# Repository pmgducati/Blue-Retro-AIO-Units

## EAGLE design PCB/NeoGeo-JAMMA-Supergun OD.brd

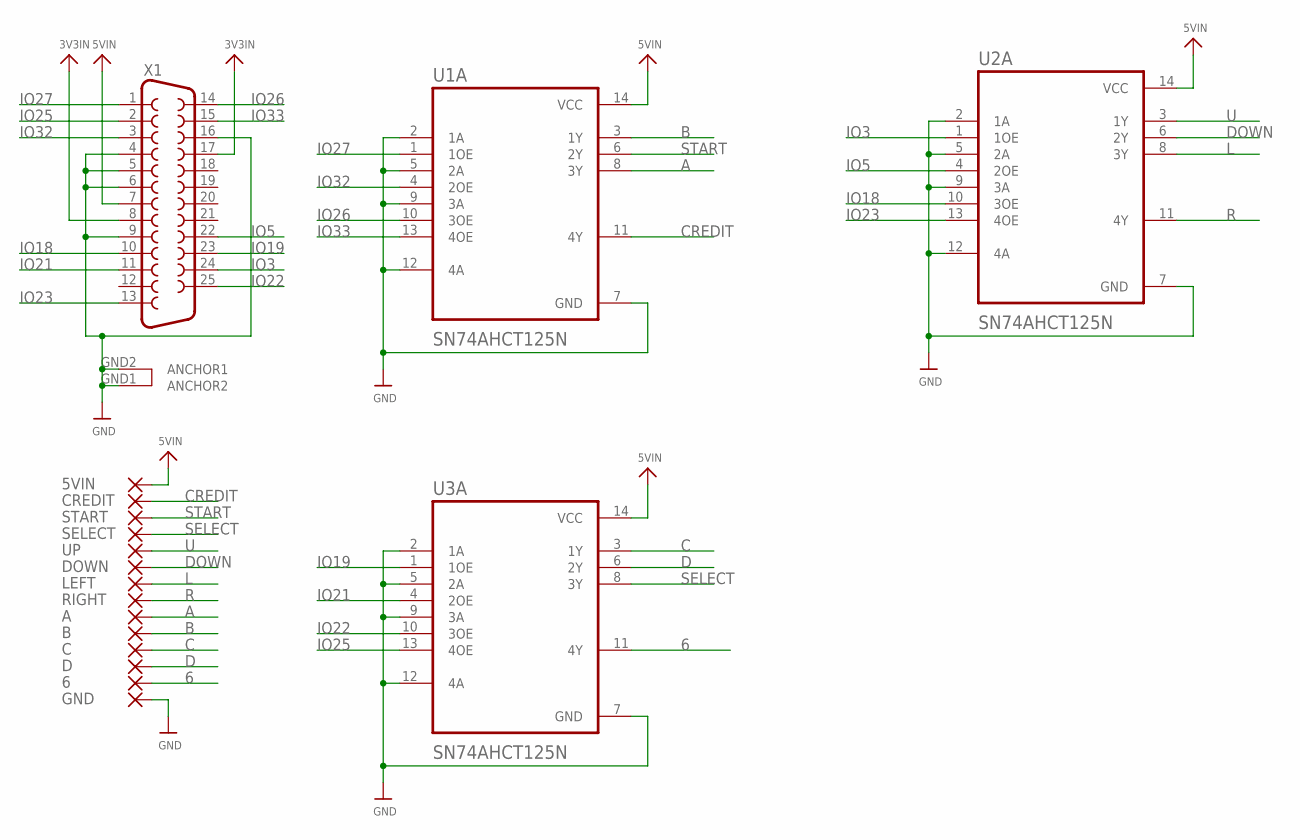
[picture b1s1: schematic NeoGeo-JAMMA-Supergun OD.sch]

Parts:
5VIN, 6: SMD5; SMD2,54-5,08
A: SMD5; SMD2,54-5,08
B: SMD5; SMD2,54-5,08
C: SMD5; SMD2,54-5,08
CREDIT: SMD5; SMD2,54-5,08
D: SMD5; SMD2,54-5,08
DOWN: SMD5; SMD2,54-5,08
GND: SMD5; SMD2,54-5,08
LEFT: SMD5; SMD2,54-5,08
RIGHT: SMD5; SMD2,54-5,08
SELECT: SMD5; SMD2,54-5,08
START: SMD5; SMD2,54-5,08
U1A, U2A, U3A: SN74AHCT125N; DIP794W45P254L1969H508Q14
UP: SMD5; SMD2,54-5,08
X1: DB25_FEMALEHP; F25HP

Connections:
3V3IN: X1.8, X1.17
5VIN: 5VIN.1, U1A.14 (VCC), U2A.14 (VCC), U3A.14 (VCC), X1.7
6: 6.1, U3A.11 (4Y)
A: A.1, U1A.8 (3Y)
B: B.1, U1A.3 (1Y)
C: C.1, U3A.3 (1Y)
CREDIT: CREDIT.1, U1A.11 (4Y)
D: D.1, U3A.6 (2Y)
DOWN: DOWN.1, U2A.6 (2Y)
GND: GND.1, U1A.2 (1A), U1A.5 (2A), U1A.7 (GND), U1A.9 (3A), U1A.12 (4A), U2A.2 (1A), U2A.5 (2A), U2A.7 (GND), U2A.9 (3A), U2A.12 (4A), U3A.2 (1A), U3A.5 (2A), U3A.7 (GND), U3A.9 (3A), U3A.12 (4A), X1.4, X1.5, X1.6, X1.9, X1.16, X1.GND1 (ANCHOR2), X1.GND2 (ANCHOR1)
IO3: U2A.1 (1OE), X1.24
IO5: U2A.4 (2OE), X1.22
IO18: U2A.10 (3OE), X1.10
IO19: U3A.1 (1OE), X1.23
IO21: U3A.4 (2OE), X1.11
IO22: U3A.10 (3OE), X1.25
IO23: U2A.13 (4OE), X1.13
IO25: U3A.13 (4OE), X1.2
IO26: U1A.10 (3OE), X1.14
IO27: U1A.1 (1OE), X1.1
IO32: U1A.4 (2OE), X1.3
IO33: U1A.13 (4OE), X1.15
L: LEFT.1, U2A.8 (3Y)
R: RIGHT.1, U2A.11 (4Y)
SELECT: SELECT.1, U3A.8 (3Y)
START: START.1, U1A.6 (2Y)
U: U2A.3 (1Y), UP.1

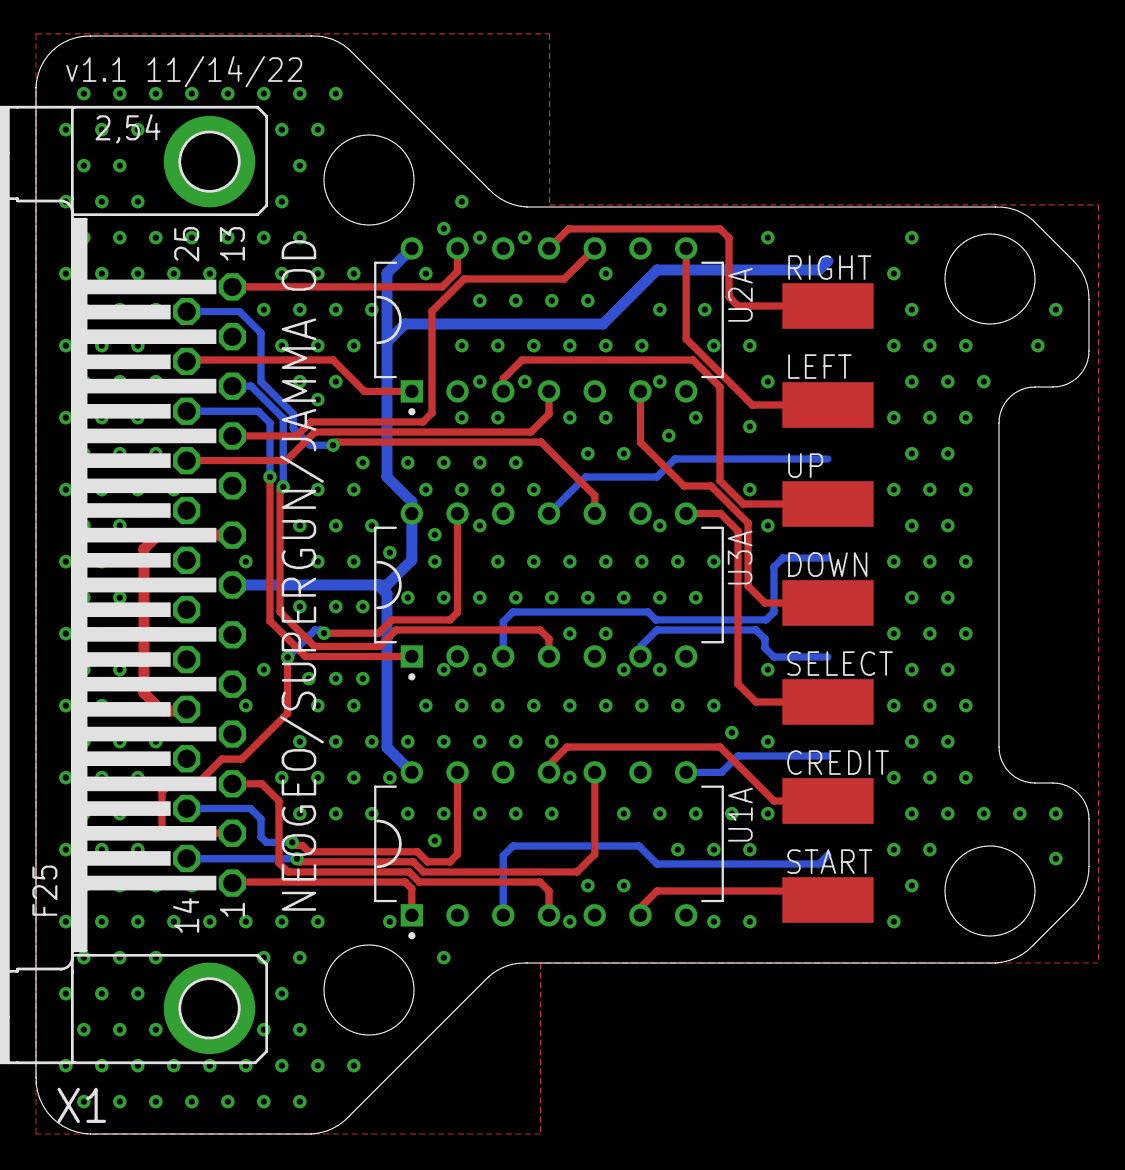
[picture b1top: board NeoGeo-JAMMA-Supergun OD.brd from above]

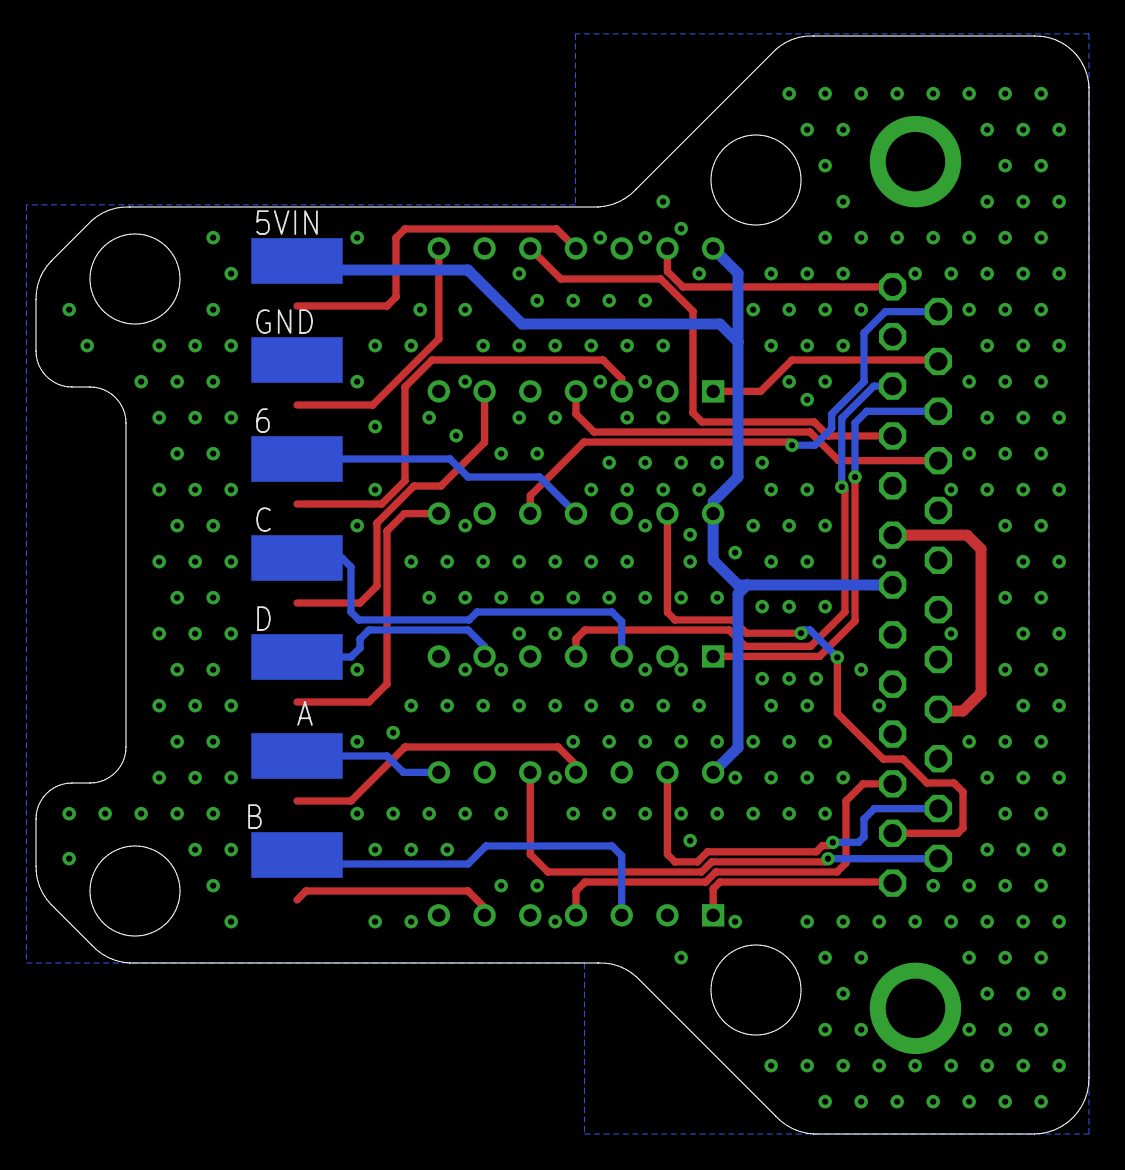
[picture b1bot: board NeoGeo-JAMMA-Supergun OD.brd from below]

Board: 2 copper layers, 58.5 x 61.0 mm, 18 parts (7 on the bottom side), 27 nets.

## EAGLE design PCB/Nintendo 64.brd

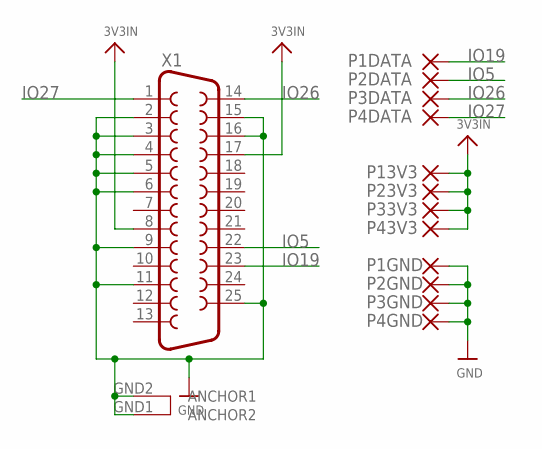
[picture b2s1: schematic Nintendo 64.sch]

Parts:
P1DATA, P1GND, P2DATA, P2GND, P3DATA, P3GND, P4DATA, P4GND, P13V3, P23V3, P33V3, P43V3: SMD5; SMD2,54-5,08
X1: DB25_FEMALEHP; F25HP

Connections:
3V3IN: P13V3.1, P23V3.1, P33V3.1, P43V3.1, X1.8, X1.17
GND: P1GND.1, P2GND.1, P3GND.1, P4GND.1, X1.2, X1.3, X1.4, X1.5, X1.6, X1.9, X1.11, X1.15, X1.16, X1.25, X1.GND1 (ANCHOR2), X1.GND2 (ANCHOR1)
IO5: P2DATA.1, X1.22
IO19: P1DATA.1, X1.23
IO26: P3DATA.1, X1.14
IO27: P4DATA.1, X1.1

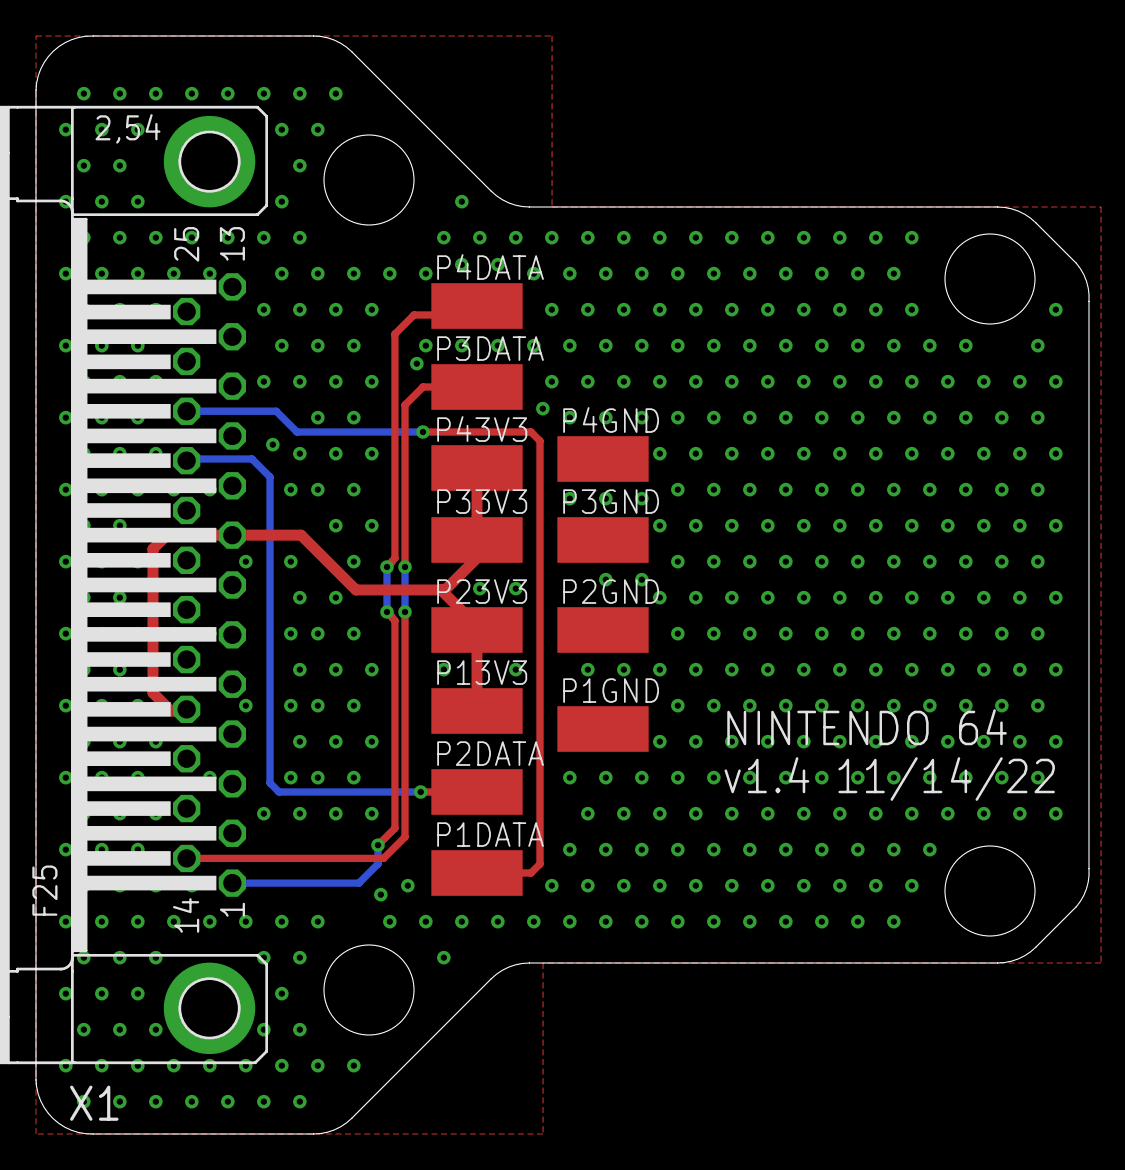
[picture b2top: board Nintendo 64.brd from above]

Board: 2 copper layers, 58.5 x 61.0 mm, 13 parts (0 on the bottom side), 6 nets.

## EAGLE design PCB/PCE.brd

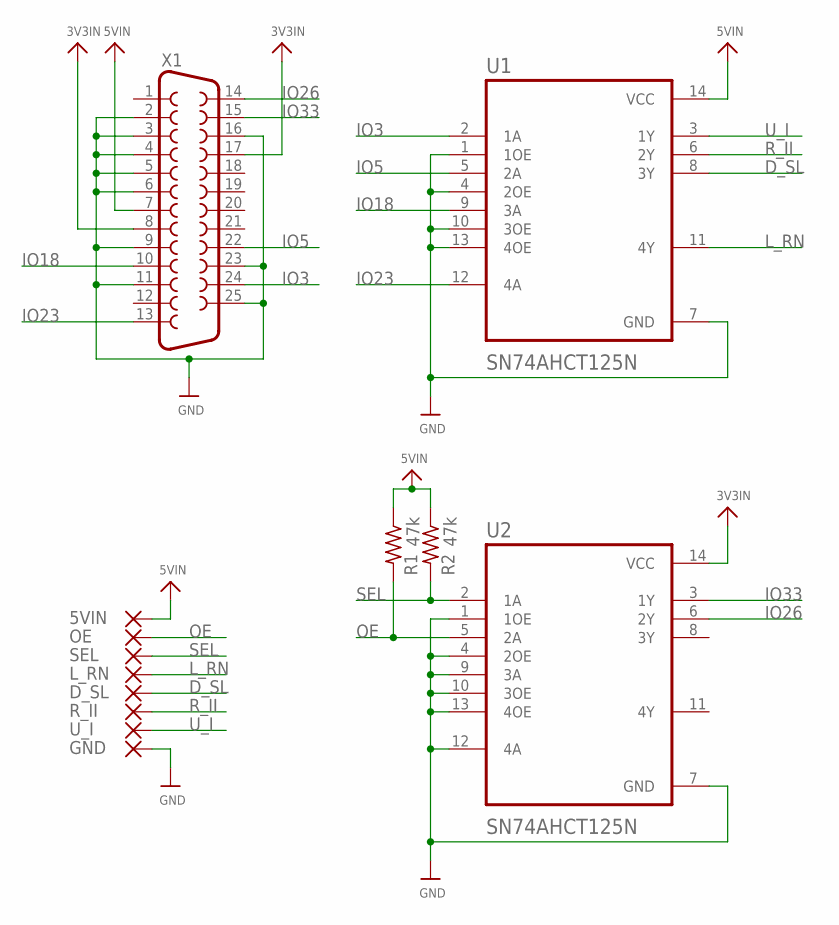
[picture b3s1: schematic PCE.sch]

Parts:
5VIN: SMD5; SMD2,54-5,08
D_SL: SMD5; SMD2,54-5,08
GND: SMD5; SMD2,54-5,08
L_RN: SMD5; SMD2,54-5,08
OE: SMD5; SMD2,54-5,08
R1, R2: 47k; R1206
R_II: SMD5; SMD2,54-5,08
SEL: SMD5; SMD2,54-5,08
U1, U2: SN74AHCT125N; DIP794W45P254L1969H508Q14
U_I: SMD5; SMD2,54-5,08
X1: DB25_FEMALEH; F25H

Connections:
3V3IN: U2.14 (VCC), X1.8, X1.17
5VIN: 5VIN.1, R1.1, R2.1, U1.14 (VCC), X1.7
D_SL: D_SL.1, U1.8 (3Y)
GND: GND.1, U1.1 (1OE), U1.4 (2OE), U1.7 (GND), U1.10 (3OE), U1.13 (4OE), U2.1 (1OE), U2.4 (2OE), U2.7 (GND), U2.9 (3A), U2.10 (3OE), U2.12 (4A), U2.13 (4OE), X1.2, X1.3, X1.4, X1.5, X1.6, X1.9, X1.11, X1.16, X1.23, X1.25
IO3: U1.2 (1A), X1.24
IO5: U1.5 (2A), X1.22
IO18: U1.9 (3A), X1.10
IO23: U1.12 (4A), X1.13
IO26: U2.6 (2Y), X1.14
IO33: U2.3 (1Y), X1.15
L_RN: L_RN.1, U1.11 (4Y)
OE: OE.1, R1.2, U2.5 (2A)
R_II: R_II.1, U1.6 (2Y)
SEL: R2.2, SEL.1, U2.2 (1A)
U_I: U1.3 (1Y), U_I.1

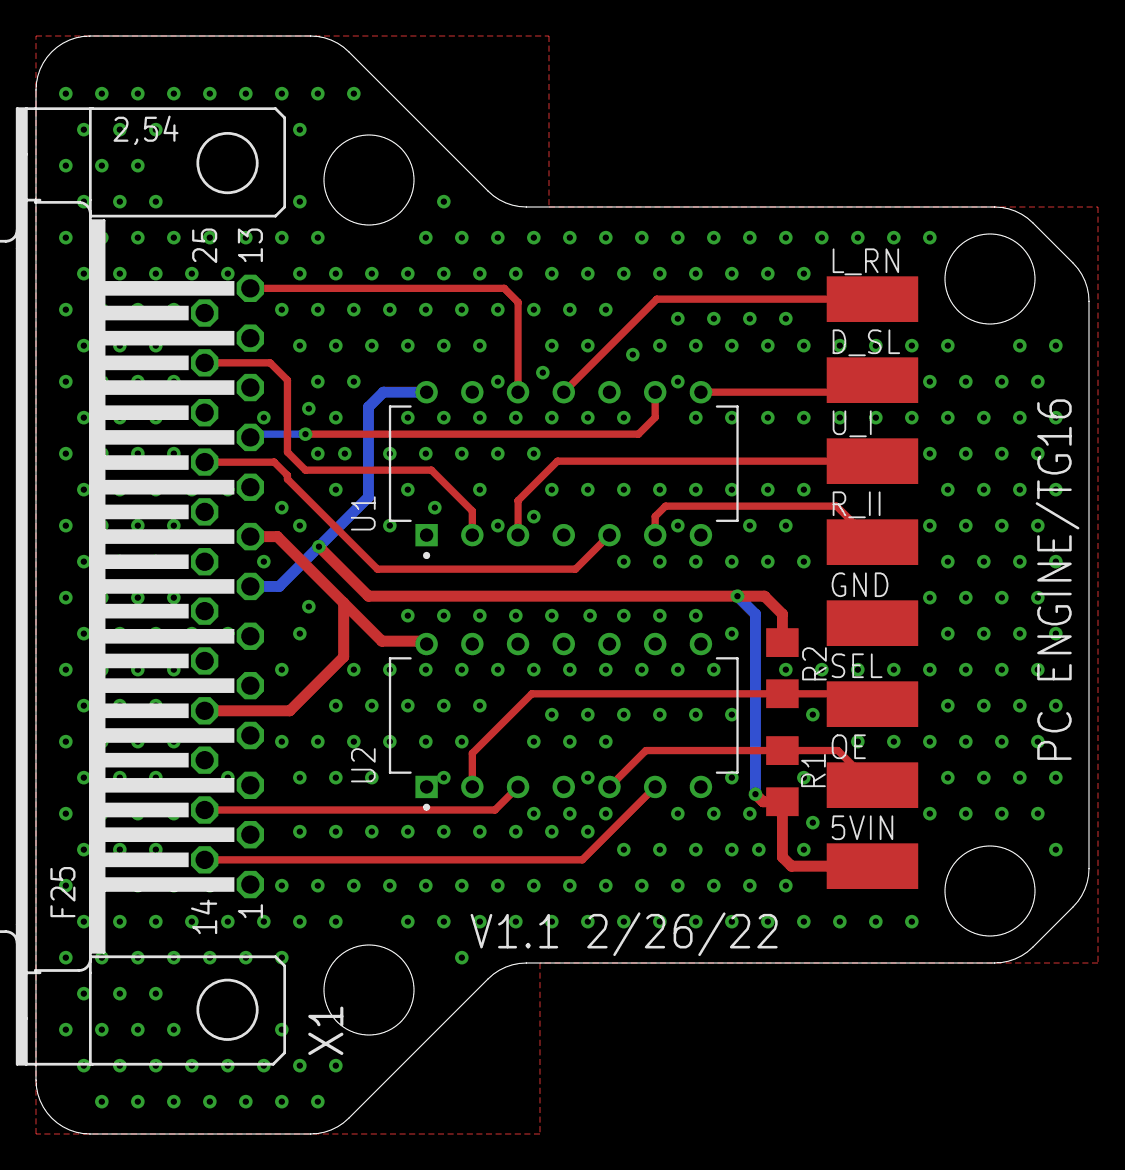
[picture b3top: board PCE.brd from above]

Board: 2 copper layers, 58.5 x 61.0 mm, 13 parts (0 on the bottom side), 15 nets.

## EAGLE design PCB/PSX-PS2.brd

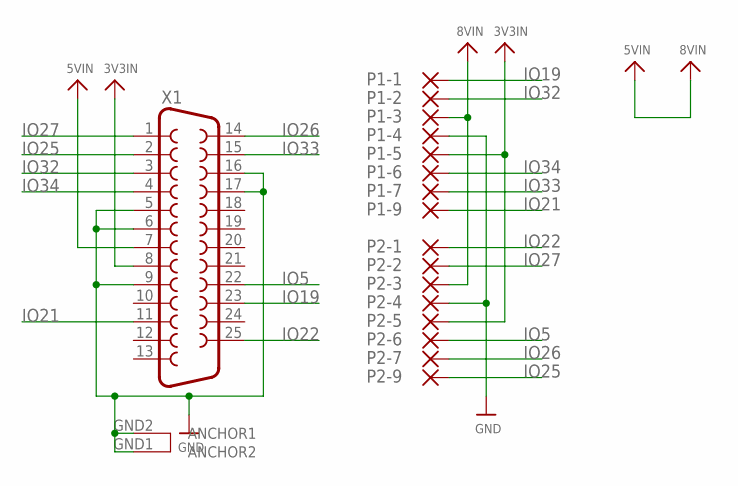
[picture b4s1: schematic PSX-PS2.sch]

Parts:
P1-1, P1-2, P1-3, P1-4, P1-5, P1-6, P1-7, P1-9, P2-1, P2-2, P2-3, P2-4, P2-5, P2-6, P2-7, P2-9: SMD5; SMD2,54-5,08
X1: DB25_FEMALEHP; F25HP

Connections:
3V3IN: P1-5.1, P2-5.1, X1.8
GND: P1-4.1, P2-4.1, X1.5, X1.6, X1.9, X1.16, X1.17, X1.GND1 (ANCHOR2), X1.GND2 (ANCHOR1)
IO5: P2-6.1, X1.22
IO19: P1-1.1, X1.23
IO21: P1-9.1, X1.11
IO22: P2-1.1, X1.25
IO25: P2-9.1, X1.2
IO26: P2-7.1, X1.14
IO27: P2-2.1, X1.1
IO32: P1-2.1, X1.3
IO33: P1-7.1, X1.15
IO34: P1-6.1, X1.4
VIN: P1-3.1, P2-3.1, X1.7

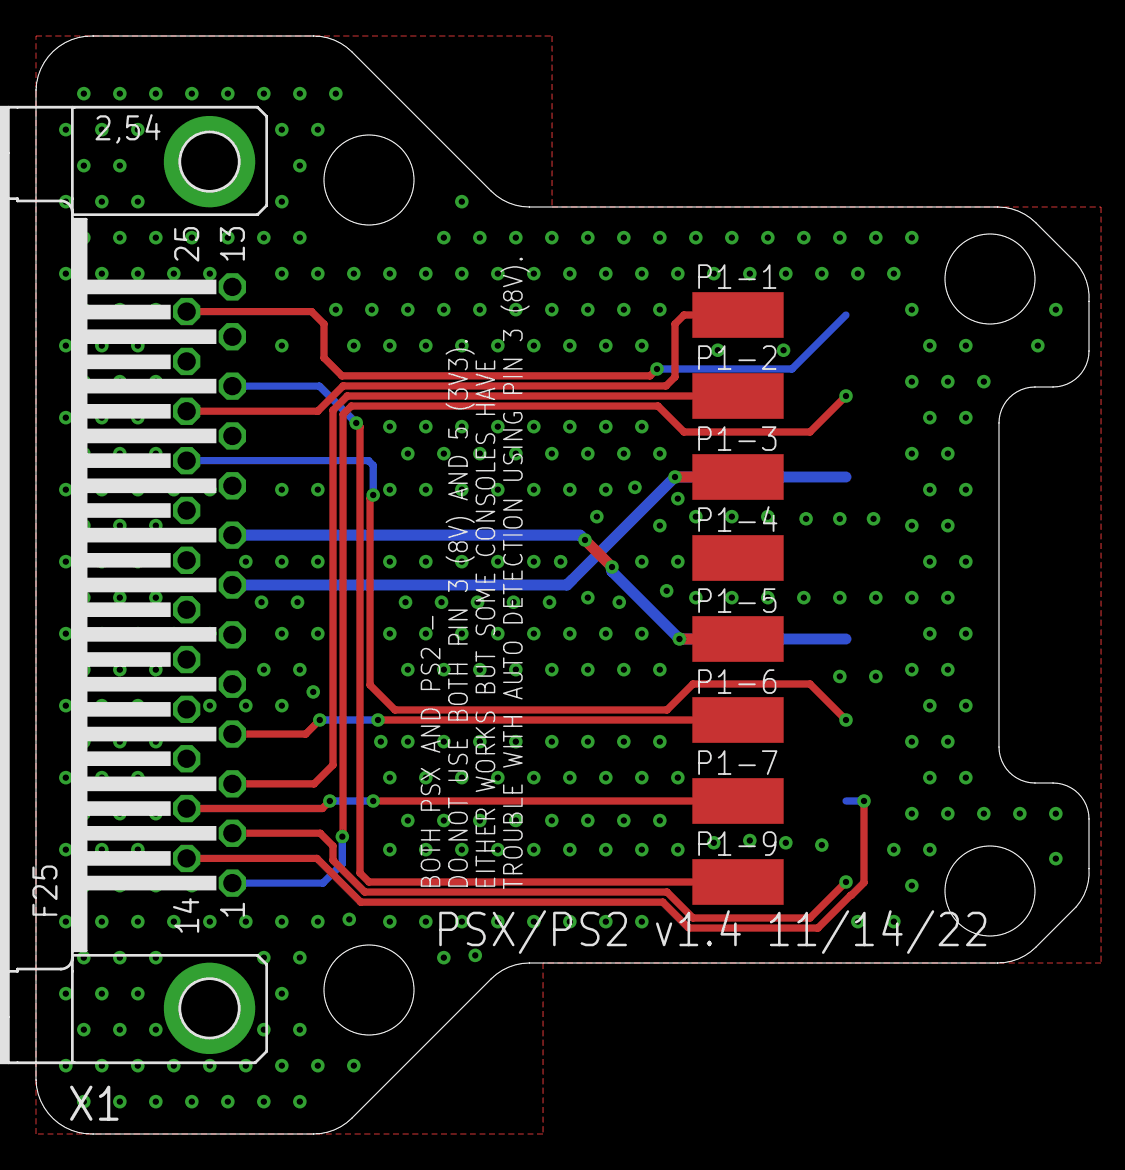
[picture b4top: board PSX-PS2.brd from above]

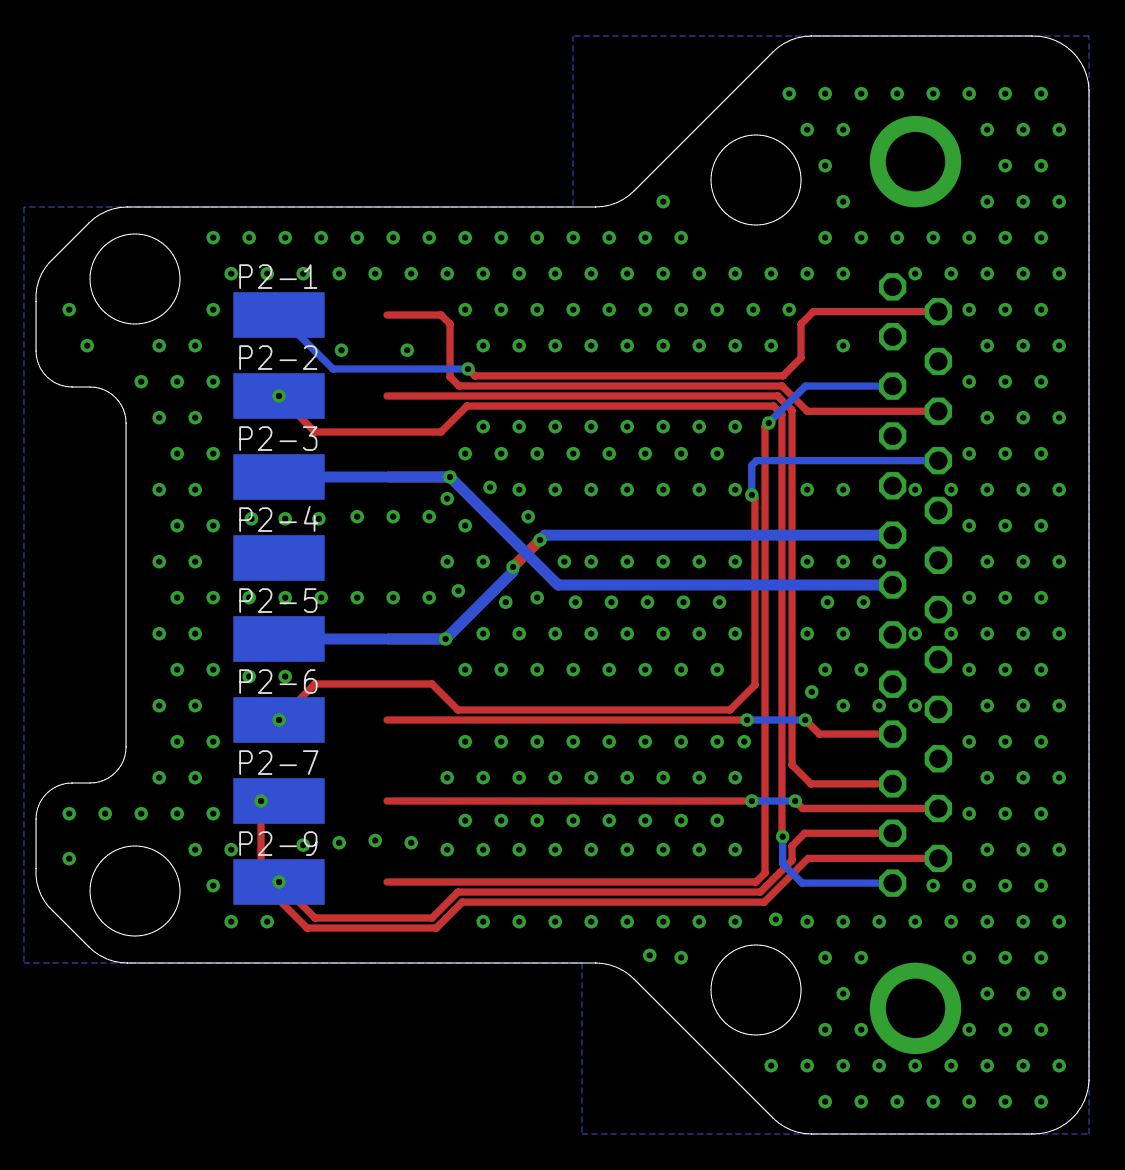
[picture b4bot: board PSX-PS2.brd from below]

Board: 2 copper layers, 58.5 x 61.0 mm, 17 parts (8 on the bottom side), 13 nets.

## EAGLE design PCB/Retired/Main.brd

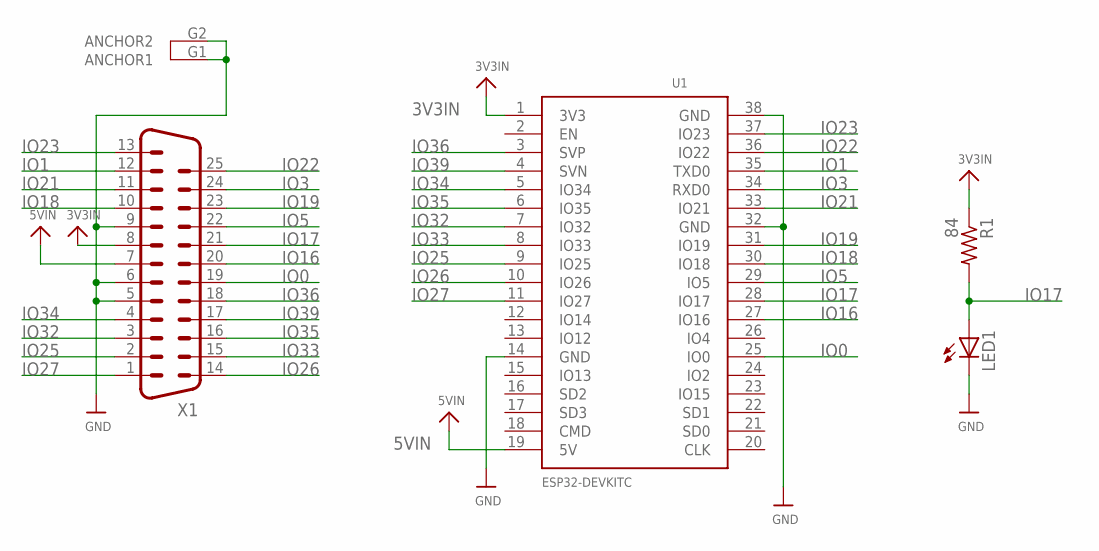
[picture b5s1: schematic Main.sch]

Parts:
LED1: LEDCHIPLED_1206; CHIPLED_1206
R1: 84; R1206
U1: ESP32DEVKITC; ESP32-DEVKITC
X1: DB25_MALEHP; M25HP

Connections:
3V3IN: R1.1, U1.1 (3V3), X1.8
5VIN: U1.19 (5V), X1.7
GND: LED1.C, U1.14 (GND), U1.32 (GND), U1.38 (GND), X1.5, X1.6, X1.9, X1.G1 (ANCHOR1), X1.G2 (ANCHOR2)
IO0: U1.25 (IO0), X1.19
IO1: U1.35 (TXD0), X1.12
IO3: U1.34 (RXD0), X1.24
IO5: U1.29 (IO5), X1.22
IO16: U1.27 (IO16), X1.20
IO17: LED1.A, R1.2, U1.28 (IO17), X1.21
IO18: U1.30 (IO18), X1.10
IO19: U1.31 (IO19), X1.23
IO21: U1.33 (IO21), X1.11
IO22: U1.36 (IO22), X1.25
IO23: U1.37 (IO23), X1.13
IO25: U1.9 (IO25), X1.2
IO26: U1.10 (IO26), X1.14
IO27: U1.11 (IO27), X1.1
IO32: U1.7 (IO32), X1.3
IO33: U1.8 (IO33), X1.15
IO34: U1.5 (IO34), X1.4
IO35: U1.6 (IO35), X1.16
IO36: U1.3 (SVP), X1.18
IO39: U1.4 (SVN), X1.17

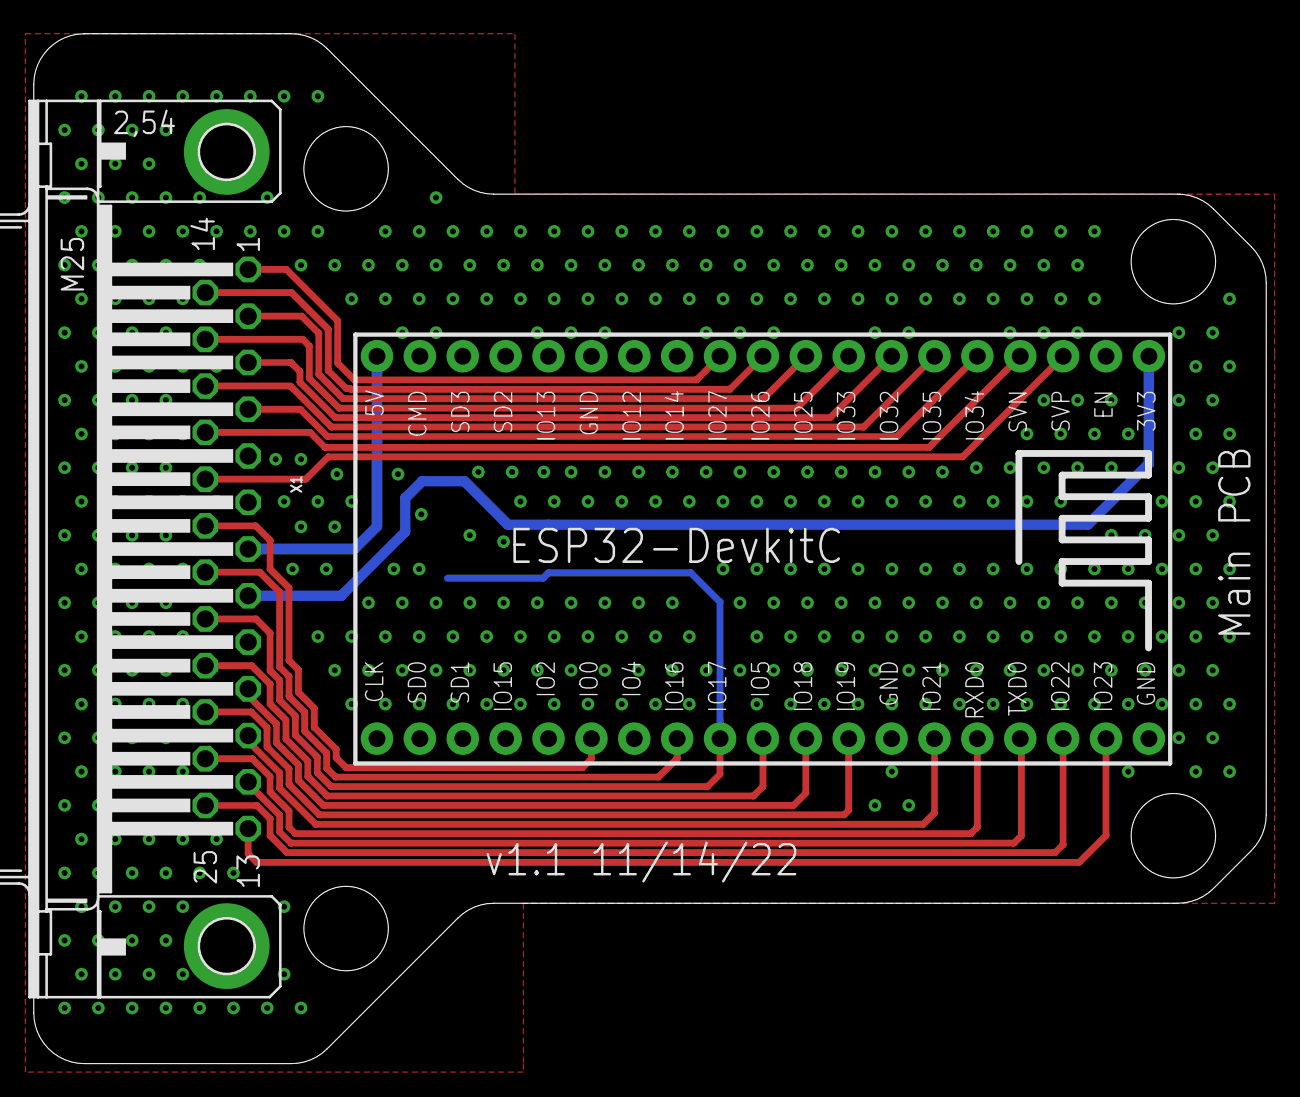
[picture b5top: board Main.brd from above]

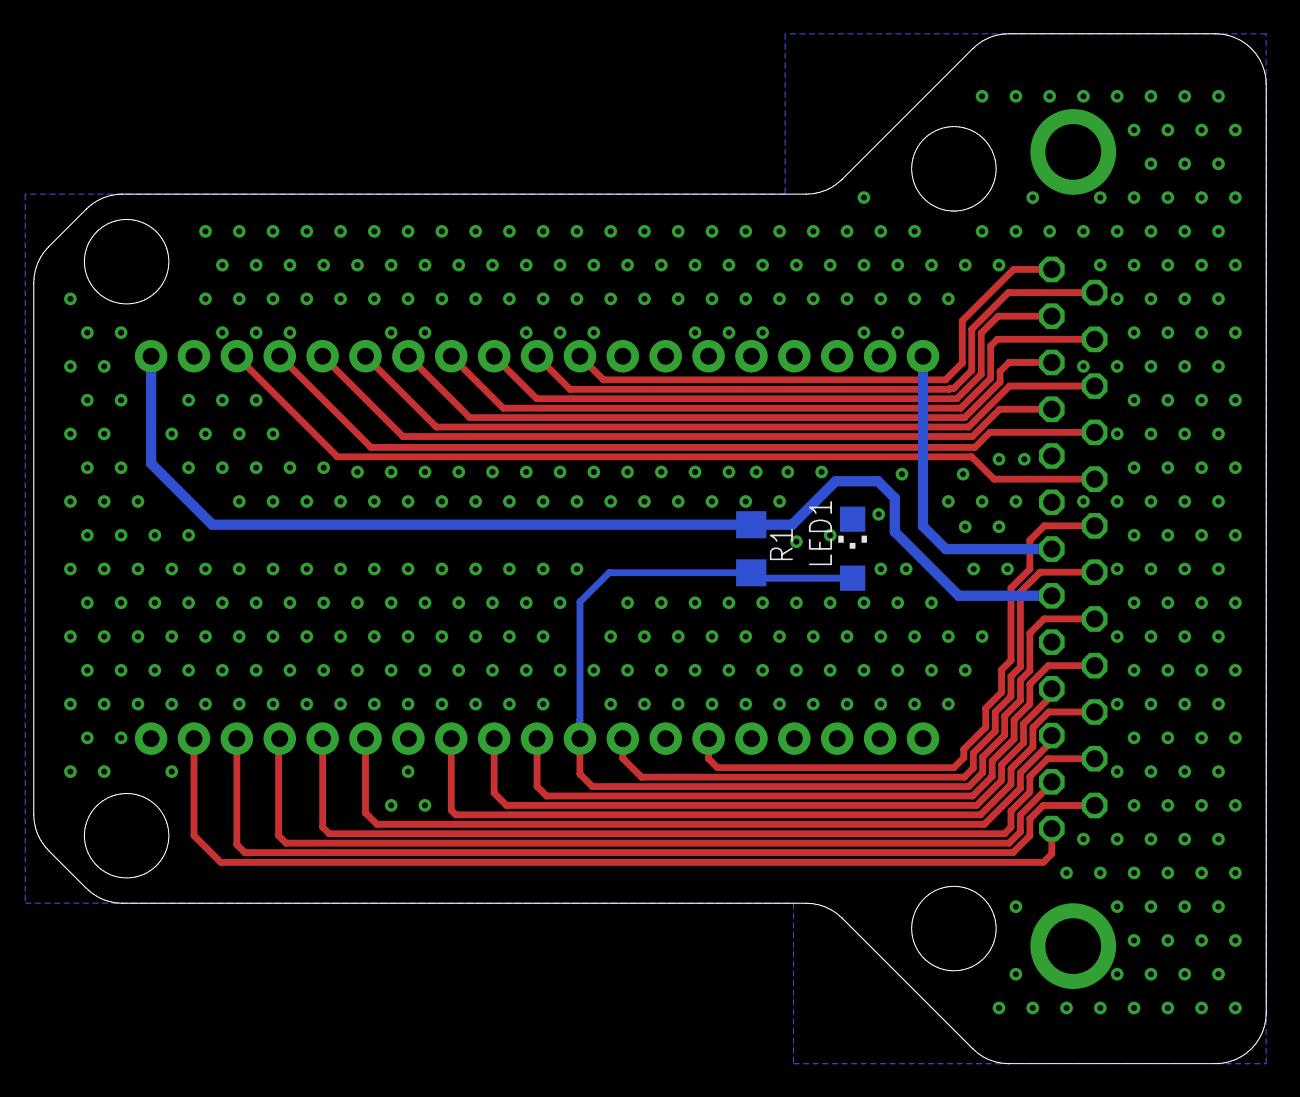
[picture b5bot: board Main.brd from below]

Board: 2 copper layers, 73.0 x 61.0 mm, 4 parts (2 on the bottom side), 23 nets.

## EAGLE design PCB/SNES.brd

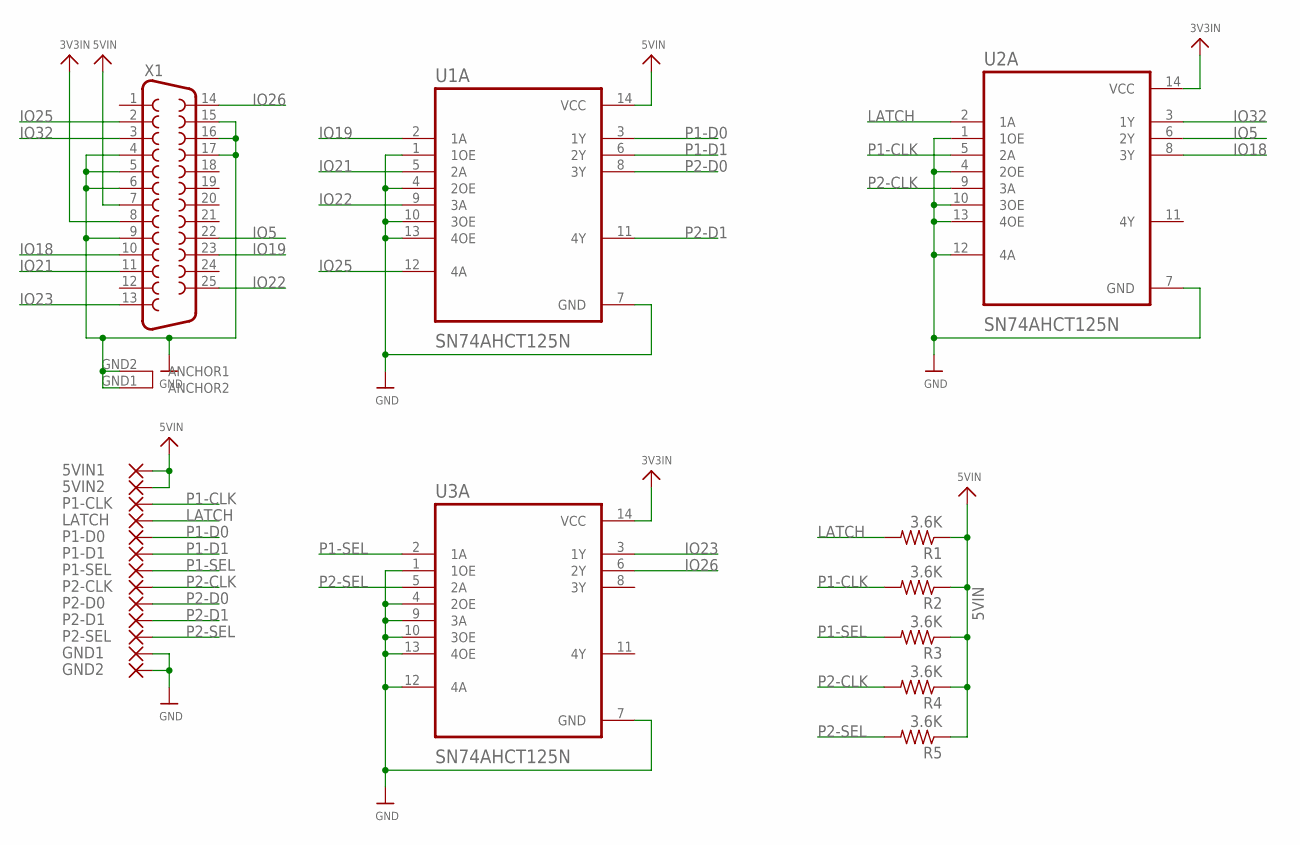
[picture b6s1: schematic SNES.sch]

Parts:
5VIN1, 5VIN2: SMD5; SMD2,54-5,08
GND1, GND2: SMD5; SMD2,54-5,08
LATCH: SMD5; SMD2,54-5,08
P1-CLK, P1-D0, P1-D1, P1-SEL, P2-CLK, P2-D0, P2-D1, P2-SEL: SMD5; SMD2,54-5,08
R1, R2, R3, R4, R5: 3.6K; R1206
U1A, U2A, U3A: SN74AHCT125N; DIP794W45P254L1969H508Q14
X1: DB25_FEMALEHP; F25HP

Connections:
3V3IN: U2A.14 (VCC), U3A.14 (VCC), X1.8
5VIN: 5VIN1.1, 5VIN2.1, R1.1, R2.1, R3.1, R4.1, R5.1, U1A.14 (VCC), X1.7
GND: GND1.1, GND2.1, U1A.1 (1OE), U1A.4 (2OE), U1A.7 (GND), U1A.10 (3OE), U1A.13 (4OE), U2A.1 (1OE), U2A.4 (2OE), U2A.7 (GND), U2A.10 (3OE), U2A.12 (4A), U2A.13 (4OE), U3A.1 (1OE), U3A.4 (2OE), U3A.7 (GND), U3A.9 (3A), U3A.10 (3OE), U3A.12 (4A), U3A.13 (4OE), X1.4, X1.5, X1.6, X1.9, X1.15, X1.16, X1.17, X1.GND1 (ANCHOR2), X1.GND2 (ANCHOR1)
IO5: U2A.6 (2Y), X1.22
IO18: U2A.8 (3Y), X1.10
IO19: U1A.2 (1A), X1.23
IO21: U1A.5 (2A), X1.11
IO22: U1A.9 (3A), X1.25
IO23: U3A.3 (1Y), X1.13
IO25: U1A.12 (4A), X1.2
IO26: U3A.6 (2Y), X1.14
IO32: U2A.3 (1Y), X1.3
LATCH: LATCH.1, R1.2, U2A.2 (1A)
P1-CLK: P1-CLK.1, R2.2, U2A.5 (2A)
P1-D0: P1-D0.1, U1A.3 (1Y)
P1-D1: P1-D1.1, U1A.6 (2Y)
P1-SEL: P1-SEL.1, R3.2, U3A.2 (1A)
P2-CLK: P2-CLK.1, R4.2, U2A.9 (3A)
P2-D0: P2-D0.1, U1A.8 (3Y)
P2-D1: P2-D1.1, U1A.11 (4Y)
P2-SEL: P2-SEL.1, R5.2, U3A.5 (2A)

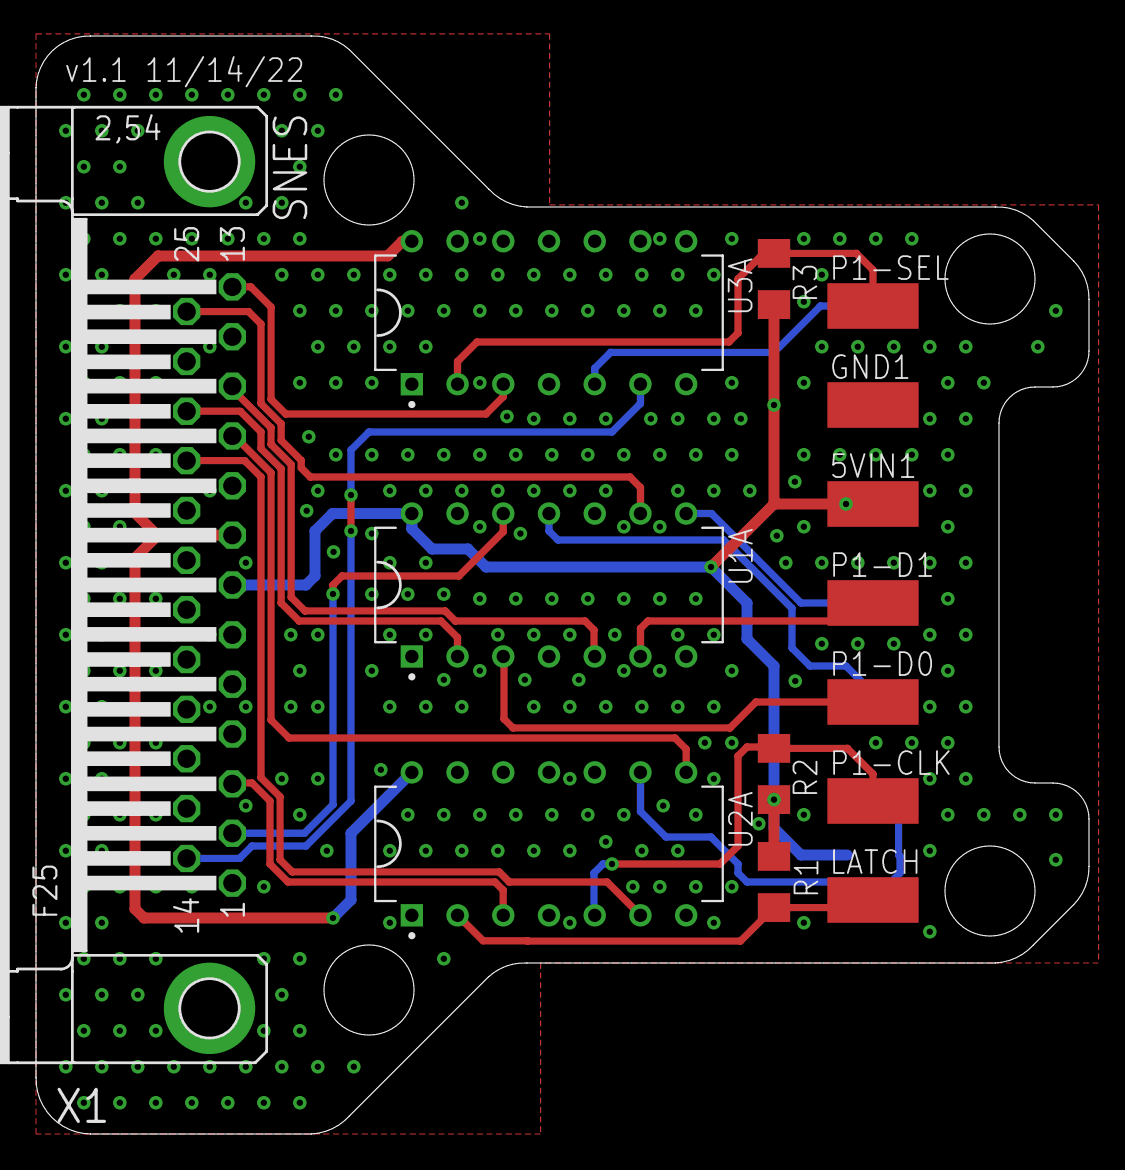
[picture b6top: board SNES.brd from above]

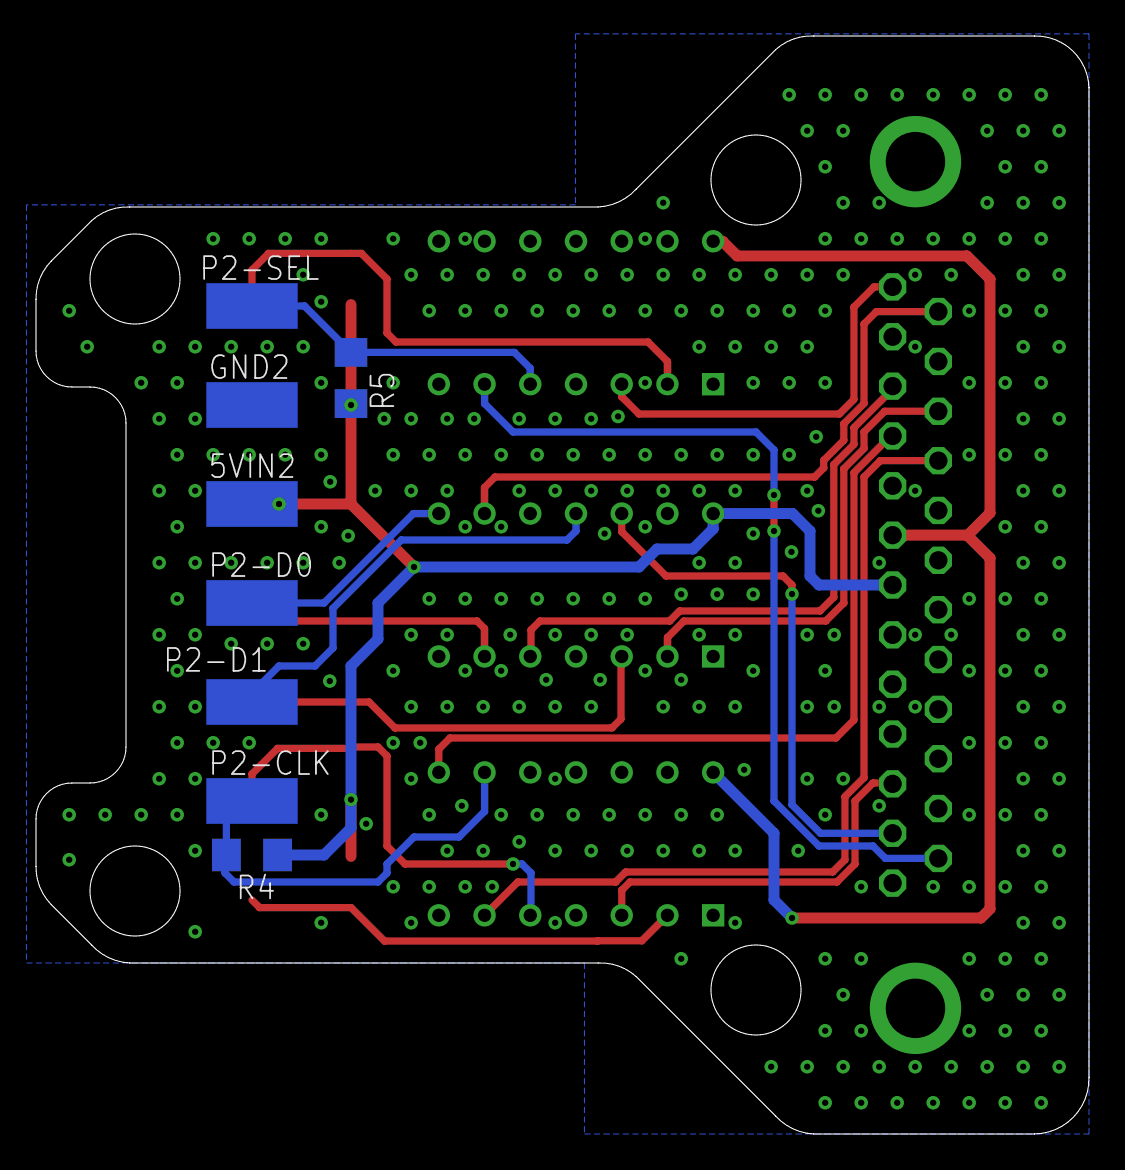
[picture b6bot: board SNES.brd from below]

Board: 2 copper layers, 58.5 x 61.0 mm, 22 parts (8 on the bottom side), 21 nets.

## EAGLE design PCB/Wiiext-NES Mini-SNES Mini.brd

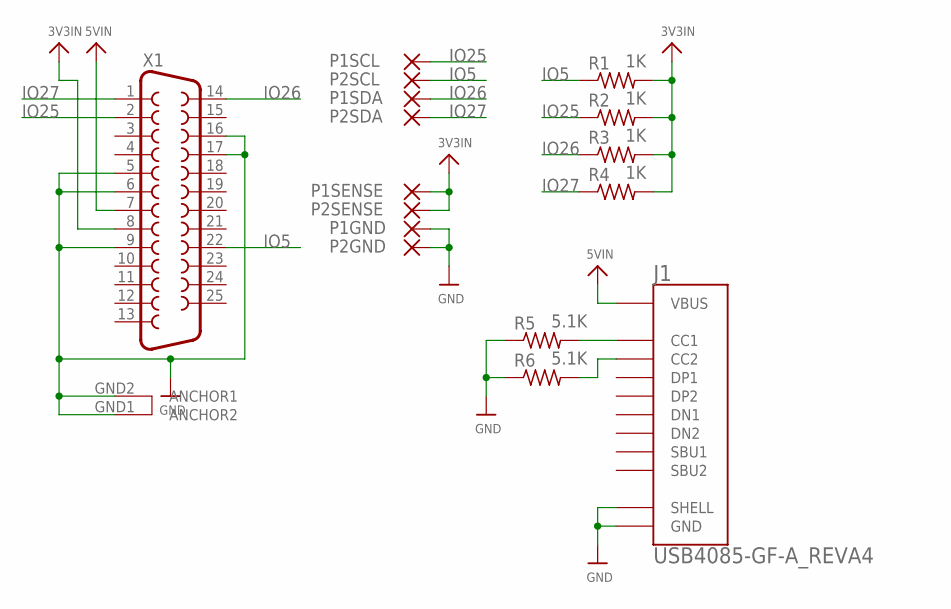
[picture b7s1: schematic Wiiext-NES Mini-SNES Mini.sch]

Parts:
J1: USB4085-GF-A_REVA4; GCT_USB4085-GF-A_REVA4
P1GND, P1SCL, P1SDA, P1SENSE, P2GND, P2SCL, P2SDA, P2SENSE: SMD5; SMD2,54-5,08
R1, R2, R3, R4: 1K; R1206
R5, R6: 5.1K; R1206
X1: DB25_FEMALEHP; F25HP

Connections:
3V3IN: P1SENSE.1, P2SENSE.1, R1.2, R2.2, R3.2, R4.2, X1.8
5VIN: J1.A4 (VBUS), J1.A9 (VBUS), J1.B4 (VBUS), J1.B9 (VBUS), X1.7
GND: J1.A1 (GND), J1.A12 (GND), J1.B1 (GND), J1.B12 (GND), J1.S1 (SHELL), J1.S2 (SHELL), J1.S3 (SHELL), J1.S4 (SHELL), P1GND.1, P2GND.1, R5.1, R6.1, X1.5, X1.6, X1.9, X1.16, X1.17, X1.GND1 (ANCHOR2), X1.GND2 (ANCHOR1)
IO5: P2SCL.1, R1.1, X1.22
IO25: P1SCL.1, R2.1, X1.2
IO26: P1SDA.1, R3.1, X1.14
IO27: P2SDA.1, R4.1, X1.1
PD1: J1.B5 (CC2), R6.2
PD2: J1.A5 (CC1), R5.2

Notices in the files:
parts and their libraries:
microbuilder: This work is placed in the public domain, and may be freely used for commercial and non-commercial work with the following conditions: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
SparkFun-Retired: Licensing: Creative Commons ShareAlike 4.0 International - https://creativecommons.org/licenses/by-sa/4.0
